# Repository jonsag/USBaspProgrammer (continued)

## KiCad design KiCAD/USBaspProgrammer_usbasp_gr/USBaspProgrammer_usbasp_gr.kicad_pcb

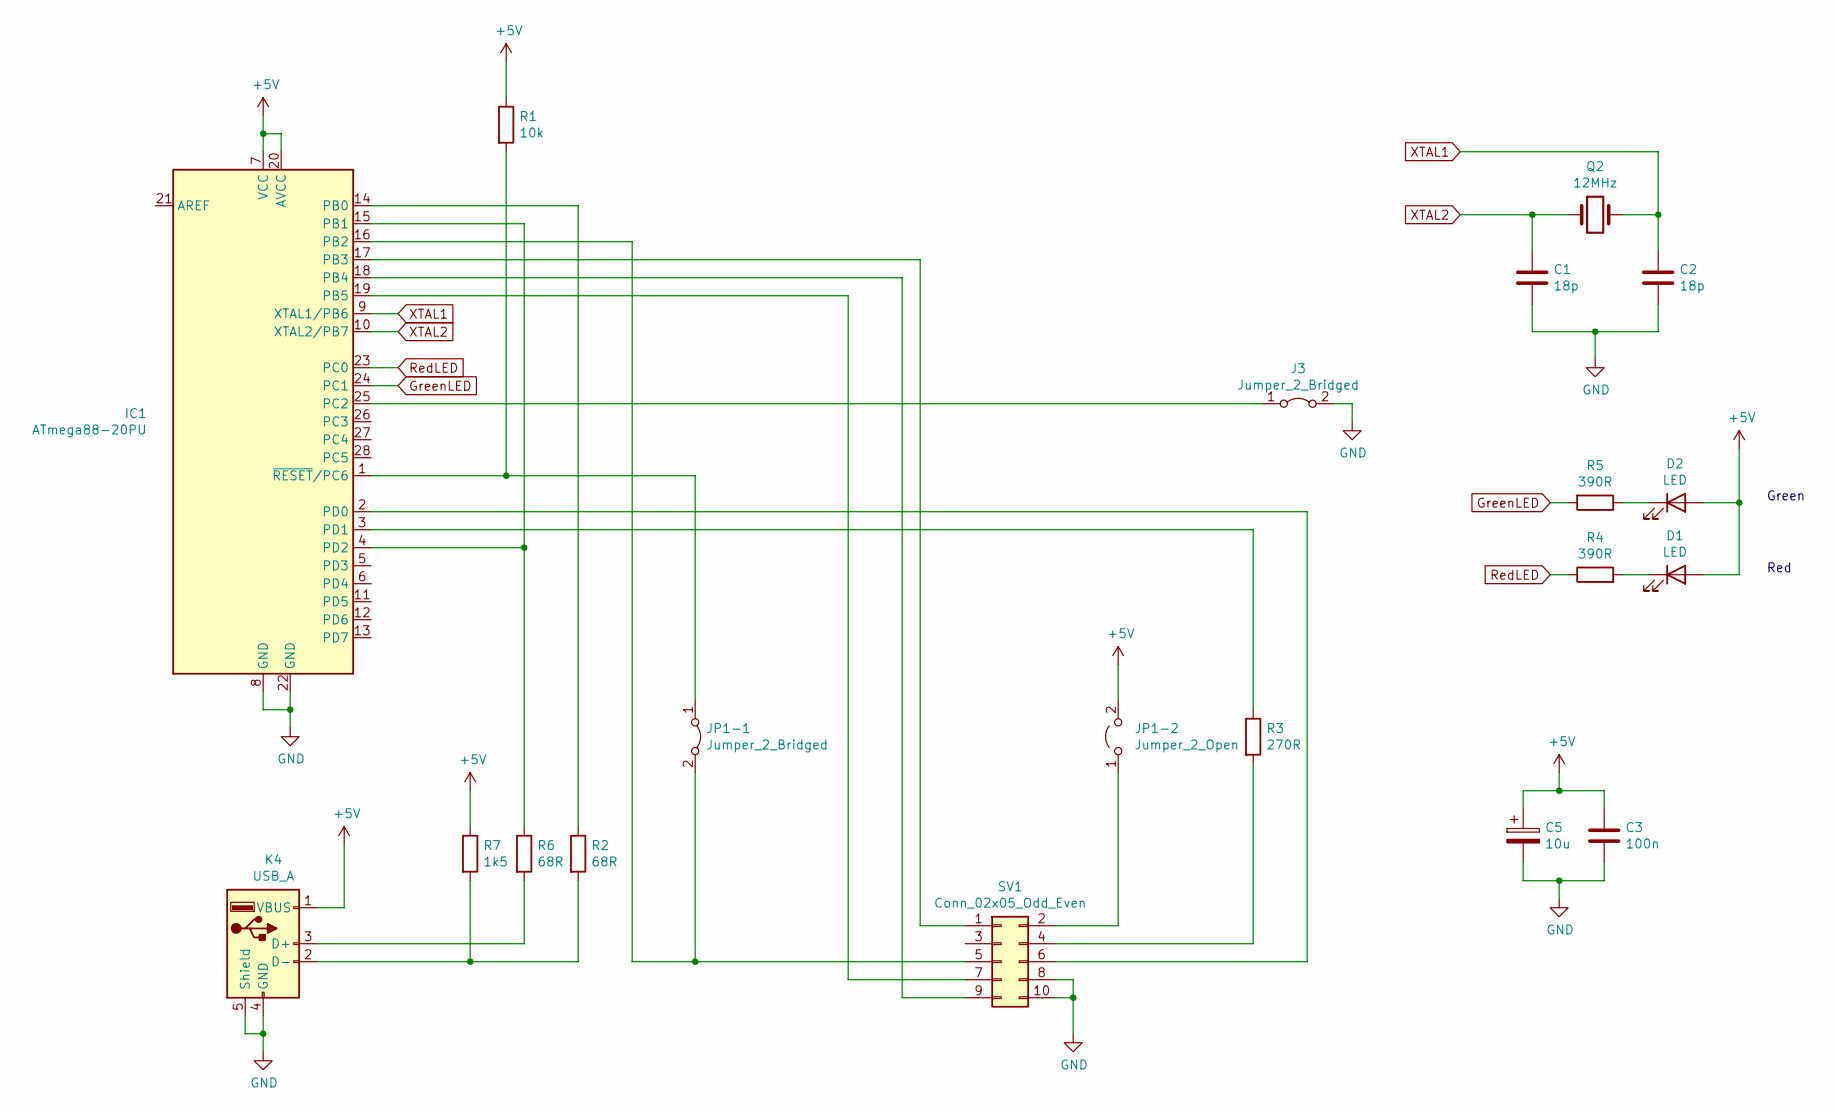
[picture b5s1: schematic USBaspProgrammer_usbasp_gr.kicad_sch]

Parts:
C1, C2: 18p; C_Disc_D3.0mm_W1.6mm_P2.50mm_larg
C3: 100n; C_Disc_D7.5mm_W2.5mm_P5.00mm_larger
C5: 10u; CP_Radial_D5.0mm_P2.00mm_larger
D1, D2: LED; LED_D5.0mm_larger_pads
IC1: ATmega88-20PU; DIP-28_W7.62mm_LongPads
J3: Jumper_2_Bridged; Jumper_1x02_P2.54mm_large
JP1-1: Jumper_2_Bridged; Jumper_1x02_P2.54mm_large
JP1-2: Jumper_2_Open; Jumper_1x02_P2.54mm_large
K4: USB_A; USB_B_Lumberg_2411_02_Horizontal_large
Q2: 12MHz; Crystal_HC49-4H_Vertical_large
R1: 10k; R_Axial_DIN0207_L6.3mm_D2.5mm_P10.16mm_Horizontal_larger_pa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
R2, R6: 68R; R_Axial_DIN0207_L6.3mm_D2.5mm_P10.16mm_Horizontal_larger_pa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
R3: 270R; R_Axial_DIN0207_L6.3mm_D2.5mm_P10.16mm_Horizontal_larger_pa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
R4, R5: 390R; R_Axial_DIN0207_L6.3mm_D2.5mm_P10.16mm_Horizontal_larger_pa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
R7: 1k5; R_Axial_DIN0207_L6.3mm_D2.5mm_P10.16mm_Horizontal_larger_pa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
SV1: Conn_02x05_Odd_Even; IDC-Header_2x05_P2.54mm_Vertical_large

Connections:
+5V: C3.1, C5.1, D1.2 (A), D2.2 (A), IC1.7 (VCC), IC1.20 (AVCC), JP1-2.2 (B), K4.1 (VBUS), R1.1, R7.1
GND: C1.2, C2.2, C3.2, C5.2, IC1.8 (GND), IC1.22 (GND), J3.2 (B), K4.4 (GND), K4.5 (Shield), SV1.8, SV1.10
GreenLED: IC1.24 (PC1), R5.2
unnamed: D1.1 (K), R4.2
unnamed: D2.1 (K), R5.1
unnamed: IC1.1 (~RESET/PC6), JP1-1.1 (A), R1.2
unnamed: IC1.2 (PD0), SV1.6
unnamed: IC1.3 (PD1), R3.1
unnamed: IC1.14 (PB0), R2.1
unnamed: IC1.4 (PD2), IC1.15 (PB1), R6.1
unnamed: IC1.16 (PB2), JP1-1.2 (B), SV1.5
unnamed: IC1.17 (PB3), SV1.1
unnamed: IC1.18 (PB4), SV1.9
unnamed: IC1.19 (PB5), SV1.7
unnamed: IC1.25 (PC2), J3.1 (A)
unnamed: JP1-2.1 (A), SV1.2
unnamed: K4.2 (D-), R2.2, R7.2
unnamed: K4.3 (D+), R6.2
unnamed: R3.2, SV1.4
RedLED: IC1.23 (PC0), R4.1
XTAL1: C2.1, IC1.9 (XTAL1/PB6), Q2.2
XTAL2: C1.1, IC1.10 (XTAL2/PB7), Q2.1

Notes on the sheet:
Green
Red

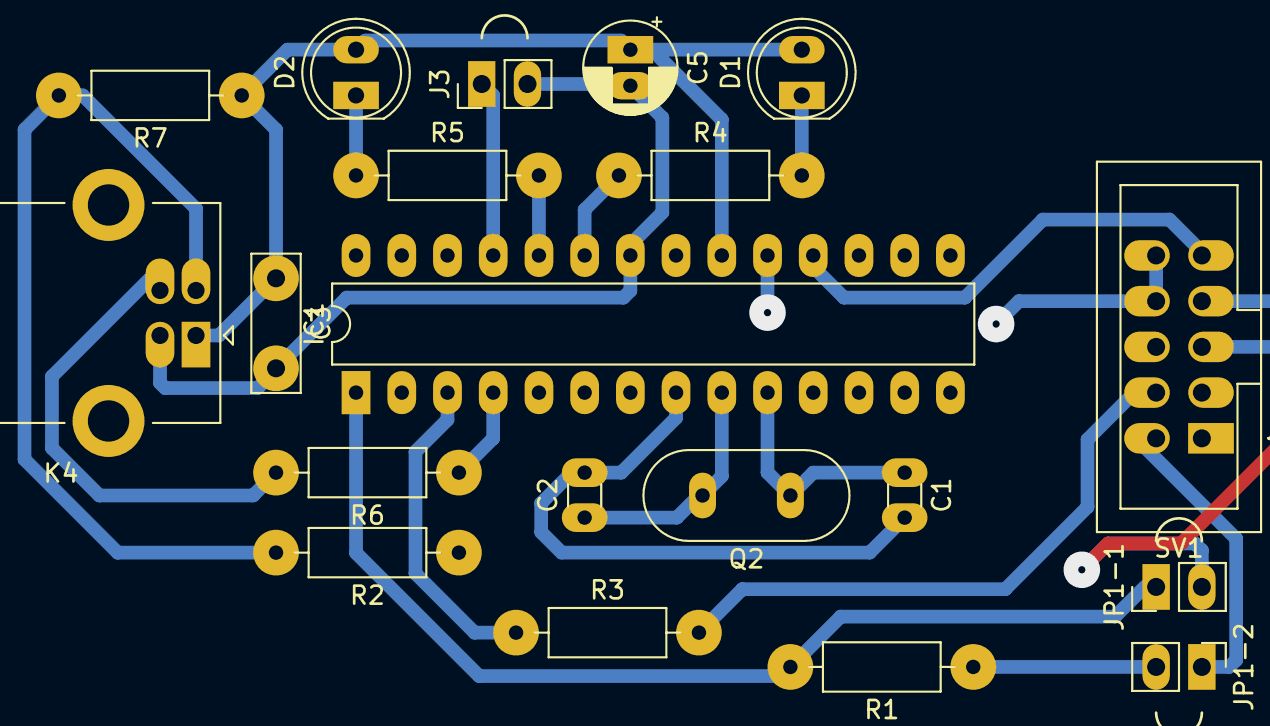
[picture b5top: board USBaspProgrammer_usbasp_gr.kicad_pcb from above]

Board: 2 copper layers, 20 parts (0 on the bottom side), 22 nets.

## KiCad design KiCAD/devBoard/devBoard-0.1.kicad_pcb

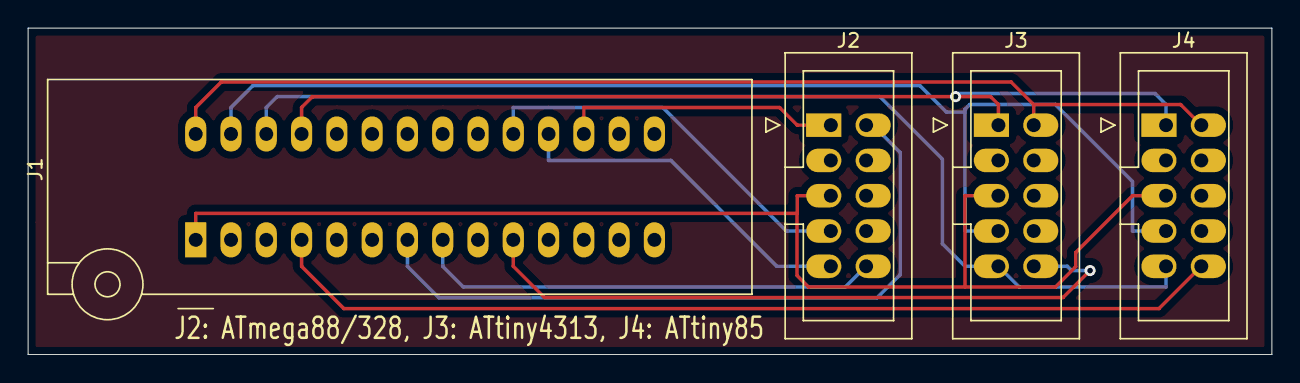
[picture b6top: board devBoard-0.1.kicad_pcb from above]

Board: 2 copper layers, 89.5 x 23.5 mm, 4 parts (0 on the bottom side), 12 nets.

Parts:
J1: Conn_02x14_Counter_Clockwise; ZIF_DIP_Socket-28_W6.9_W7.62_W7.62_W12.7_W13.5_large
J2, J3, J4: ISP_header_Conn_02x05_Odd_Even; IDC-Header_2x05_P2.54mm_Vertical_large

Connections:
1: J1.1, J2.5, J3.5, J4.5
4: J1.4, J4.10
7: J1.7, J2.2
8: J1.8, J2.10
10: J1.10, J3.10
17: J1.17, J2.1
18: J1.18, J2.9
19: J1.19, J2.7
25: J1.25, J3.1, J4.1
26: J1.26, J3.9, J4.9
27: J1.27, J3.7, J4.7
28: J1.28, J3.2, J4.2

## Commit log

2021-02-16 Fixed problem with compile error
2021-02-17 devBoard
2021-02-17 Makefile and readmes
2021-02-17 devBoard, gerbers
2021-02-18 New PCBs
2021-02-20 dev board
2021-03-09 howto
2021-10-16 Readme
2022-03-04 new kicad version
2022-03-04 deletions
2022-03-04 kicad 6
2022-03-19 new dev board
2022-05-17 kicad
2025-01-10 workspace file
2025-01-29 schematics and pcb
2025-02-02 new gitignore
